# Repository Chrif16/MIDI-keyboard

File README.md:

# BONE PIANO

a midi piano that plugs into your computer and you're able to play any music you want by touching the copper traces on the pcb. containing an esp32 s3 and 3 customizable buttons and a potentiometer slider. and it also comes equipped with a screen that visualizes your note playing in waveform. its also skeleton themed because of the halloween season.
this is a part of hackclub's half life event in which i got help in starting out with a guide.

# Schematics
the micro controller used is a waveshare esp32 s3 zero because it has more gpio pins than the c3 which was my first choice but then as the components increased i found myself having to cut a bunch of features i waanted to have but i couldnt fit it all into my board, the display is a standart 0.96 inch oled

# pcb
the main gimmick with this build is the capacitive touch keys that are made of copper so when your body(that can pass current) touches it, it can detect which button was pressed 

# 3D model
the case isnt really necessary but if you want to protect the pcb you can use it i guess, but regrdless i thing it came out looking great unfortunately i didnt have enough time to make it halloween themed too

# firmware
i used the kmk firmware like the guide recommended and i definetly learned something new with how these type of projects work

the challenge with this part of the project was trying to incorporate all of the input devices at the same time, and also definetly trying to understand how to use kmk was a real pain, and also also making the script that makes the waveform was tough

# BOM
|number of parts|part                           |link                                                                                                                                                                                                                                                                                                                                                                                                                                                                                                                                                                                                                                                              |price |
|---------------|-------------------------------|------------------------------------------------------------------------------------------------------------------------------------------------------------------------------------------------------------------------------------------------------------------------------------------------------------------------------------------------------------------------------------------------------------------------------------------------------------------------------------------------------------------------------------------------------------------------------------------------------------------------------------------------------------------|------|
|1              |waveshare esp32 s3 zero        |https://www.aliexpress.us/item/3256806776731157.html?spm=a2g0o.productlist.main.15.482a56e3AFkoUe&algo_pvid=272920cd-6205-4073-8e20-afeb743c3d61&algo_exp_id=272920cd-6205-4073-8e20-afeb743c3d61-14&pdp_ext_f=%7B%22order%22%3A%22953%22%2C%22eval%22%3A%221%22%2C%22fromPage%22%3A%22search%22%7D&pdp_npi=6%40dis%21USD%2155.12%2149.96%21%21%2155.12%2149.96%21%402103274a17929683436936034e0dba%2112000051721448210%21sea%21US%210%21ABX%211%210%21n_tag%3A-29910%3Bd%3A3c3ee12f%3Bm03_new_user%3A-29895%3BpisId%3A5000000218152484&curPageLogUid=C42bl997dEIB&utparam-url=scene%3Asearch%7Cquery_from%3A%7Cx_object_id%3A1005006963045909%7C_p_origin_prod%3A|$4.29 |
|1              |Bourns Slide Potentiometers    |https://www.aliexpress.us/item/3256809451173049.html?spm=a2g0o.detail.0.0.4ae7UuB2UuB2Zy&mp=1&pdp_npi=6%40dis%21USD%21USD+2.58%21USD+2.32%21%21USD+2.32%21%21%21%400b15841617929692304533667e102c%2112000049717901325%21ct%21US%21-1%21%211%210%21&gatewayAdapt=glo2usa                                                                                                                                                                                                                                                                                                                                                                                           |$2.58 |
|1              |0.96 inch oled display         |https://www.aliexpress.us/item/3256806795691296.html?spm=a2g0o.productlist.main.9.27e74926l4ebKm&algo_pvid=fd58b686-06b4-4867-bf45-206dadc1584d&algo_exp_id=fd58b686-06b4-4867-bf45-206dadc1584d-8&pdp_ext_f=%7B%22order%22%3A%2233%22%2C%22eval%22%3A%221%22%2C%22fromPage%22%3A%22search%22%7D&pdp_npi=6%40dis%21USD%214.82%211.09%21%21%2132.01%217.28%21%402103128817929689347392562e0d77%2112000038930846105%21sea%21US%210%21ABX%211%210%21n_tag%3A-29910%3Bd%3A3c3ee12f%3Bm03_new_user%3A-29895%3BpisId%3A5000000218152484&curPageLogUid=JsZNF58BaPaz&utparam-url=scene%3Asearch%7Cquery_from%3A%7Cx_object_id%3A1005006982006048%7C_p_origin_prod%3A      |$5    |
|3              |Kailh Choc Low-Profile Switches|https://www.aliexpress.us/item/3256812653947991.html?spm=a2g0o.productlist.0.0.35d43c5fJWn5m3&mp=1&pdp_npi=6%40dis%21USD%21USD+4.36%21USD+4.36%21%21USD+4.36%21%21%21%400b15841617929692238543568e102c%2112000059499320560%21ct%21US%21-1%21%211%210%21&gatewayAdapt=glo2usa                                                                                                                                                                                                                                                                                                                                                                                      |$4.36 |
|5              |pcb                            |jlcpcb                                                                                                                                                                                                                                                                                                                                                                                                                                                                                                                                                                                                                                                            |$4    |
|1              |3d printing                    |jlcp                                                                                                                                                                                                                                                                                                                                                                                                                                                                                                                                                                                                                                                              |$2    |
|               |total                          |                                                                                                                                                                                                                                                                                                                                                                                                                                                                                                                                                                                                                                                                  |$22.23|

# How to build:
flash your microcontroller with the .bin file in the firmware first, then upload the rest of the files on the drive that shows up on your computer then solder all the compontnents in their place. then and only then do you put on your 3d printed case and screw the back of it in place and then enjoy your very own skeleton guitar.

# zine

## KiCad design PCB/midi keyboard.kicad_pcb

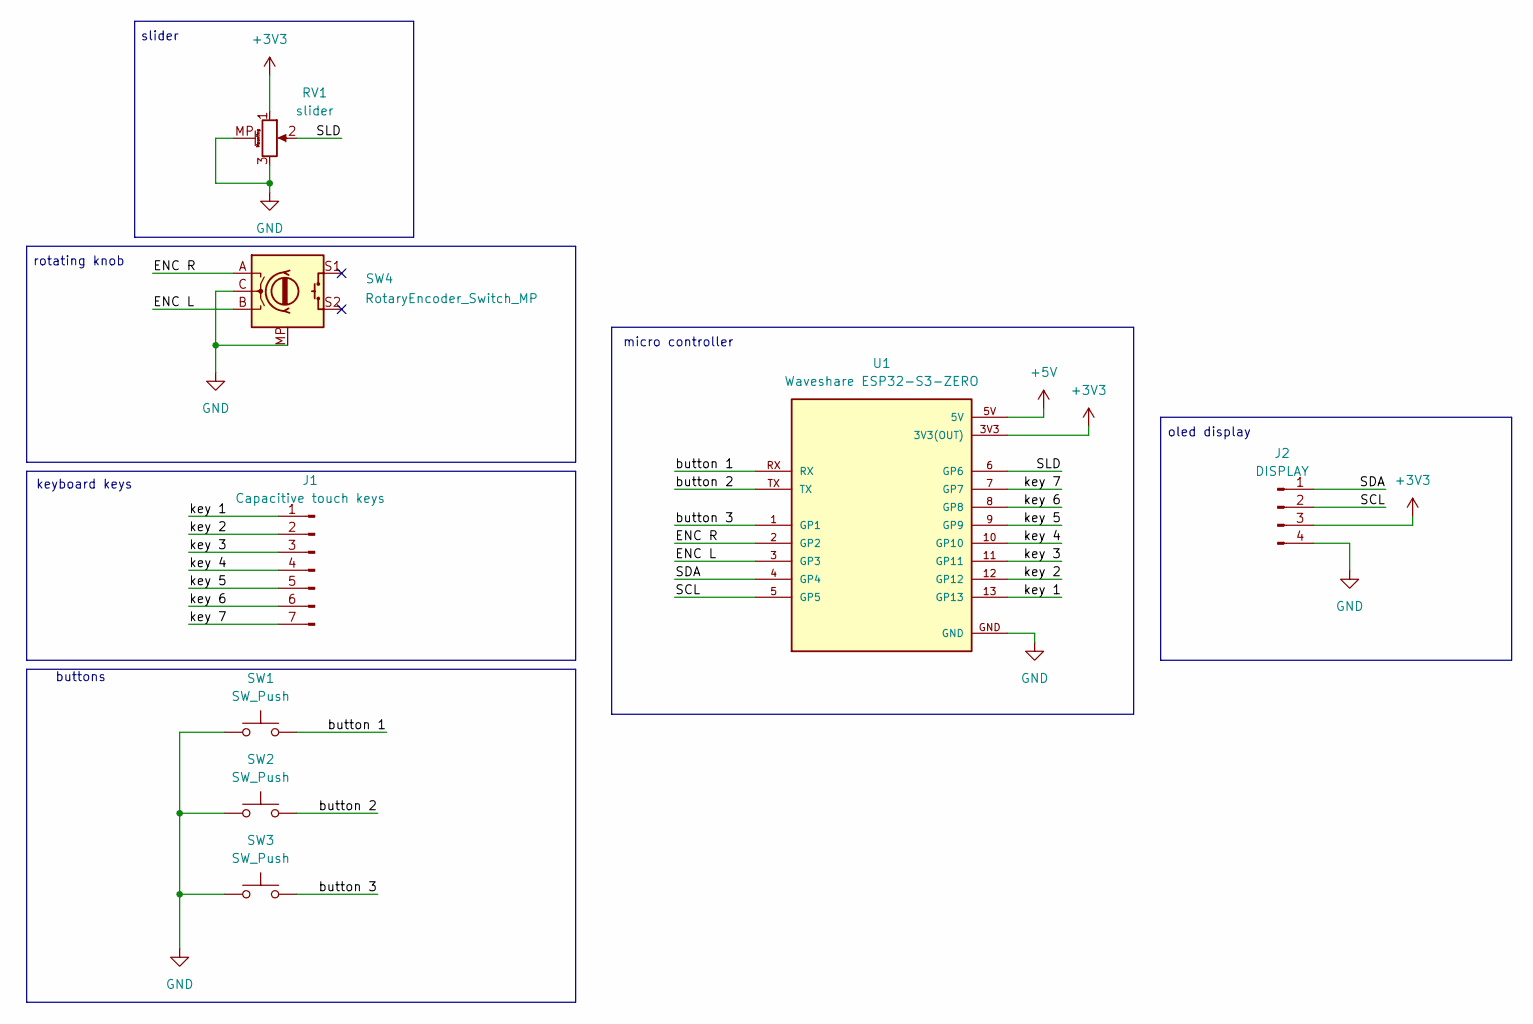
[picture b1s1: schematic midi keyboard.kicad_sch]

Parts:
J1: Capacitive touch keys; keys
J2: DISPLAY; Display_128x64_096_I2C
RV1: slider; Potentiometer_Bourns_PTA1543_Single_Slide
SW1, SW2, SW3: SW_Push; Kailh Choc Low-Profile Switches
SW4: RotaryEncoder_Switch_MP; RotaryEncoder_Alps_EC11E_Vertical_H20mm
U1: Waveshare ESP32-S3-ZERO; Waveshare ESP32-S3-Zero; PARTREV NA

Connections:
+3V3: J2.3, RV1.1, U1.3V3 (3V3(OUT))
+5V: U1.5V
/ENC L: SW4.B, U1.3 (GP3)
/ENC R: SW4.A, U1.2 (GP2)
/SCL: J2.2, U1.5 (GP5)
/SDA: J2.1, U1.4 (GP4)
/SLD: RV1.2, U1.6 (GP6)
/button 1: SW1.2, U1.RX
/button 2: SW2.2, U1.TX
/button 3: SW3.2, U1.1 (GP1)
/key 1: J1.1, U1.13 (GP13)
/key 2: J1.2, U1.12 (GP12)
/key 3: J1.3, U1.11 (GP11)
/key 4: J1.4, U1.10 (GP10)
/key 5: J1.5, U1.9 (GP9)
/key 6: J1.6, U1.8 (GP8)
/key 7: J1.7, U1.7 (GP7)
GND: J2.4, RV1.3, RV1.MP (MountPin), SW1.1, SW2.1, SW3.1, SW4.C, SW4.MP, U1.GND

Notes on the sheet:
keyboard keys
buttons
micro controller
slider
rotating knob
oled display

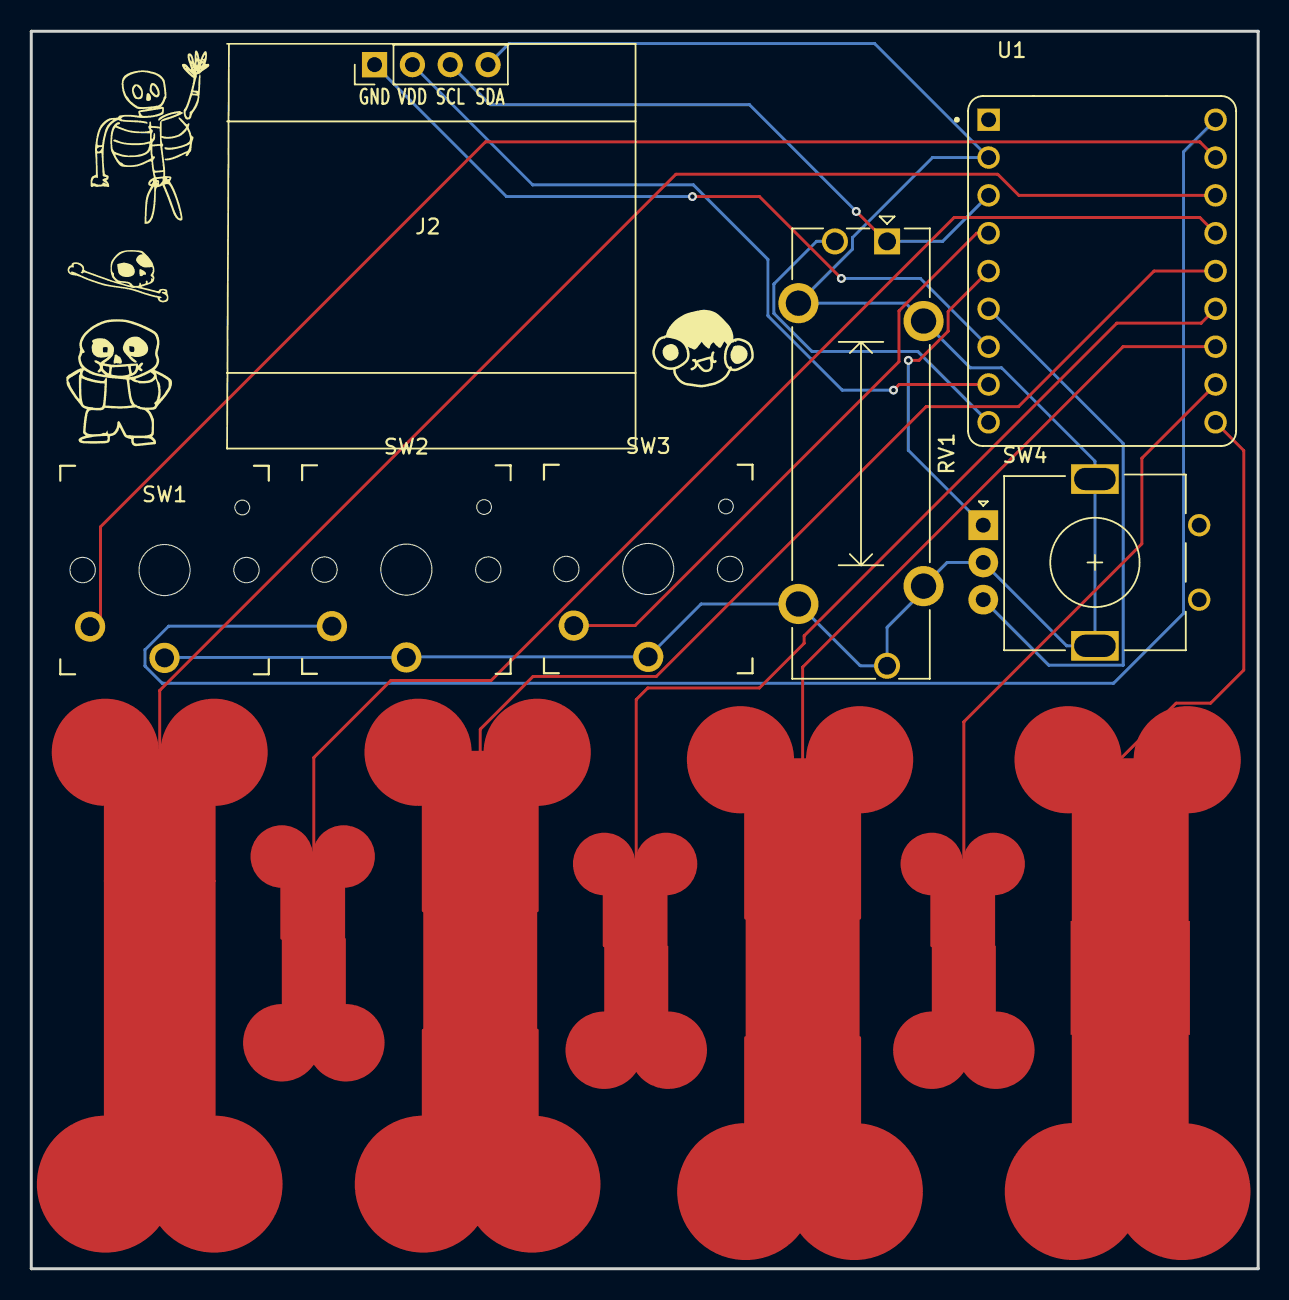
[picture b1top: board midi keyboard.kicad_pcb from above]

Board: 2 copper layers, 82.4 x 83.1 mm, 8 parts (0 on the bottom side), 17 nets.
